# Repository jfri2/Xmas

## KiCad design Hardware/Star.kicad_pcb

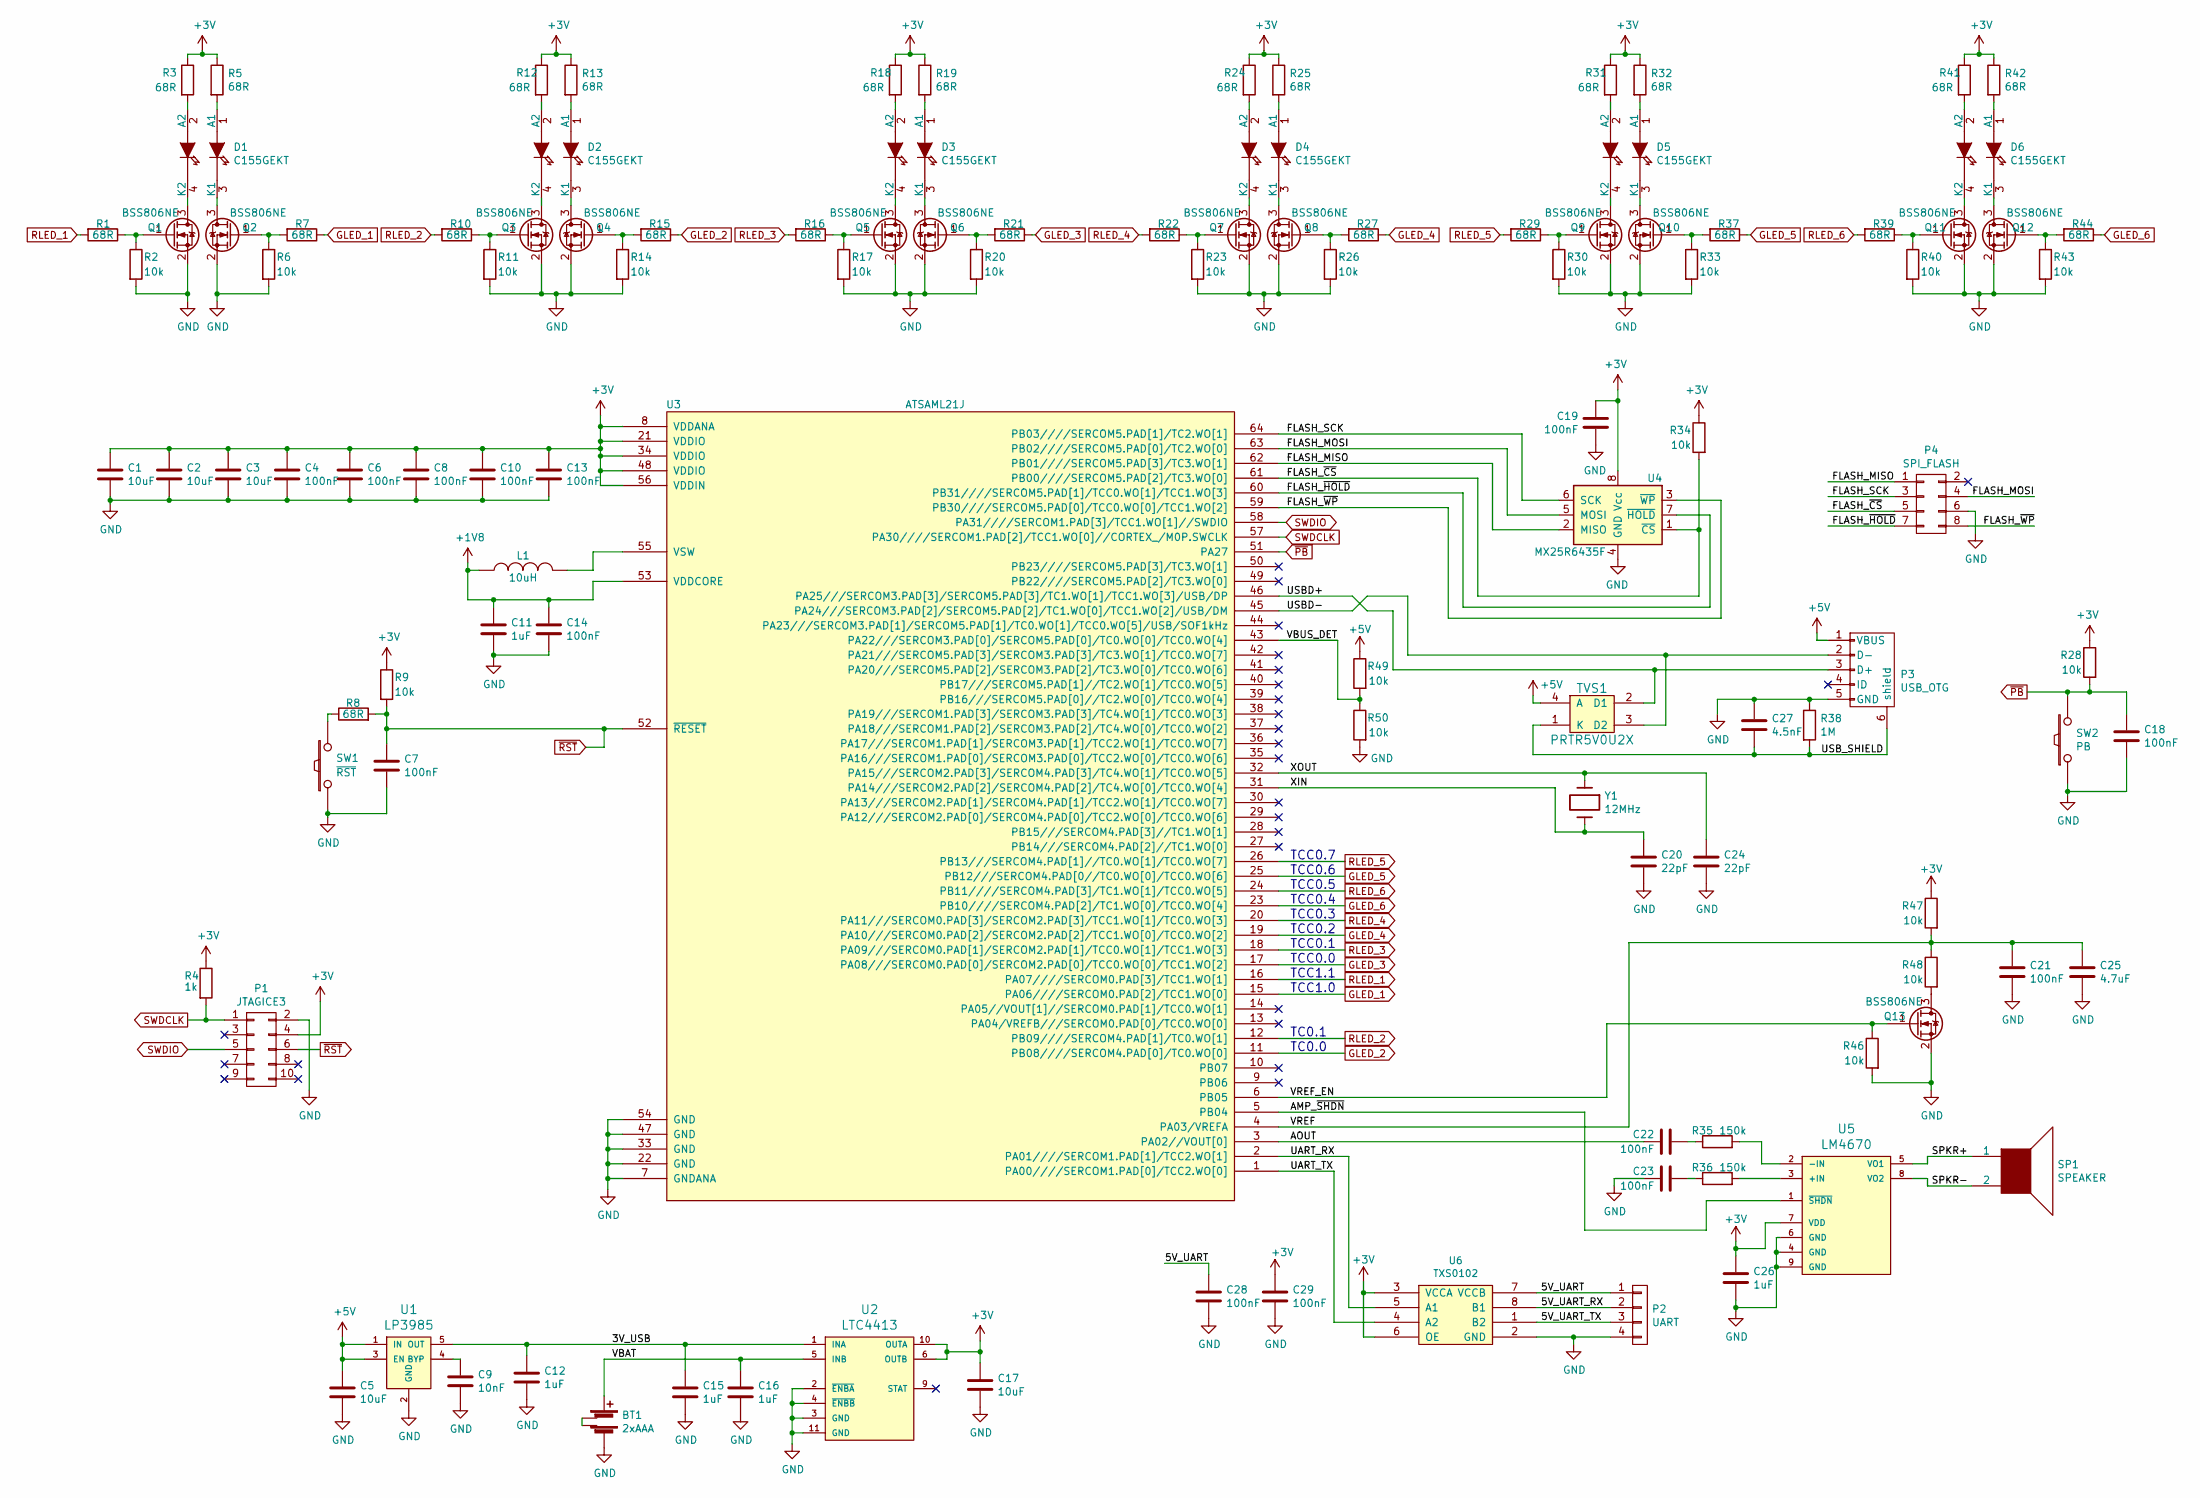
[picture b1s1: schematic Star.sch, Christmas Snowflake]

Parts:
BT1: 2xAAA; DUAL_AAA_HOLDER
C1, C2, C3, C5, C17: 10uF; C_1206
C4, C6, C7, C8, C10, C13, C14, C18, C19, C21, C22, C23, C28, C29: 100nF; C_0603
C9: 10nF; C_1206
C11, C12, C15, C16, C26: 1uF; C_0805
C20, C24: 22pF; C_0603
C25: 4.7uF; C_0805
C27: 4.5nF; C_0603
D1, D2, D3, D4, D5, D6: C155GEKT; LED2
L1: 10uH; Inductor_3mmx3mm
P1: JTAGICE3; Pin_Header_Straight_2x05_Pitch1.27mm
P2: UART; Pin_Header_Straight_1x04
P3: USB_OTG; conn_usb_B_micro_smd
P4: SPI_FLASH; Pin_Header_Straight_2x04
Q1, Q2, Q3, Q4, Q5, Q6, Q7, Q8, Q9, Q10, Q11, Q12, Q13: BSS806NE; SOT-23
R1, R3, R5, R7, R8, R10, R12, R13, R15, R16, R18, R19, R21, R22, R24, R25, R27, R29, R31, R32, R37, R39, R41, R42, R44: 68R; C_0603
R2, R6, R9, R11, R14, R17, R20, R23, R26, R28, R30, R33, R34, R40, R43, R46, R47, R48, R49, R50: 10k; C_0603
R4: 1k; C_0603
R35, R36: 150k; C_0603
R38: 1M; C_0603
SP1: SPEAKER; AS01808MR-R
SW1: ~RST; SW_SPST_TL3342
SW2: PB; SW_SPST_TL3342
TVS1: PRTR5V0U2X; SOT143B
U1: LP3985; SOT-23-5
U2: LTC4413; DFN-10-1EP_3x3mm_Pitch0.5mm
U3: ATSAML21J; QFN-64-1EP_9x9mm_Pitch0.5mm
U4: MX25R6435F; SOIJ-8_5.3x5.3mm_Pitch1.27mm
U5: LM4670; DFN-8-1EP_3x3mm_Pitch0.5mm
U6: TXS0102; MSOP-8_3x3mm_Pitch0.65mm
Y1: 12MHz; Crystal_SMD_5032_4Pads

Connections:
+1V8: C11.1, C14.1, L1.1, U3.53 (VDDCORE)
+3V: C1.1, C2.1, C3.1, C4.1, C6.1, C8.1, C10.1, C13.1, C17.1, C19.1, C26.1, C29.1, P1.4, R3.1, R4.1, R5.1, R9.1, R12.1, R13.1, R18.1, R19.1, R24.1, R25.1, R28.1, R31.1, R32.1, R34.1, R41.1, R42.1, R47.1, U2.6 (OUTB), U2.10 (OUTA), U3.8 (VDDANA), U3.21 (VDDIO), U3.34 (VDDIO), U3.48 (VDDIO), U3.56 (VDDIN), U4.8 (Vcc), U5.7 (VDD), U6.3 (VCCA), U6.6 (OE)
+5V: C5.1, P3.1 (VBUS), R49.1, TVS1.4 (A), U1.1 (IN), U1.3 (EN)
/3V_USB: C12.1, C15.1, U1.5 (OUT), U2.1 (INA)
/5V_UART: C28.1, P2.1, U6.7 (VCCB)
/5V_UART_RX: P2.2, U6.8 (B1)
/5V_UART_TX: P2.3, U6.1 (B2)
/AMP_~SHDN: U3.5 (PB04), U5.1 (~SHDN)
/AOUT: C22.1, U3.3 (PA02//VOUT[0])
/FLASH_MISO: P4.1, U3.62 (PB01////SERCOM5.PAD[3]/TC3.WO[1]), U4.2 (MISO)
/FLASH_MOSI: P4.4, U3.63 (PB02////SERCOM5.PAD[0]/TC2.WO[0]), U4.5 (MOSI)
/FLASH_SCK: P4.3, U3.64 (PB03////SERCOM5.PAD[1]/TC2.WO[1]), U4.6 (SCK)
/FLASH_~CS: P4.5, R34.2, U3.61 (PB00////SERCOM5.PAD[2]/TC3.WO[0]), U4.1 (~CS)
/FLASH_~HOLD: P4.7, U3.60 (PB31////SERCOM5.PAD[1]/TCC0.WO[1]/TCC1.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), U4.7 (~HOLD)
/FLASH_~WP: P4.8, U3.59 (PB30////SERCOM5.PAD[0]/TCC0.WO[0]/TCC1.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), U4.3 (~WP)
/SPKR+: SP1.1, U5.5 (VO1)
/SPKR-: SP1.2, U5.8 (VO2)
/UART_RX: U3.2 (PA01////SERCOM1.PAD[1]/TCC2.WO[1]), U6.5 (A1)
/UART_TX: U3.1 (PA00////SERCOM1.PAD[0]/TCC2.WO[0]), U6.4 (A2)
/USBD+: P3.3 (D+), TVS1.2 (D1), U3.46 (PA25///SERCOM3.PAD[3]/SERCOM5.PAD[3]/TC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)
/USBD-: P3.2 (D-), TVS1.3 (D2), U3.45 (PA24///SERCOM3.PAD[2]/SERCOM5.PAD[2]/TC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)
/USB_SHIELD: C27.2, P3.6 (shield), R38.2, TVS1.1 (K)
/VBAT: BT1.4, C16.1, U2.5 (INB)
/VBUS_DET: R49.2, R50.1, U3.43 (PA22///SERCOM3.PAD[0]/SERCOM5.PAD[0]/TC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)
/VREF: C21.1, C25.1, R47.2, R48.1, U3.4 (PA03/VREFA)
/VREF_EN: Q13.1 (G), R46.1, U3.6 (PB05)
/XIN: C20.1, U3.31 (PA14///SERCOM2.PAD[2]/SERCOM4.PAD[2]/TC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), Y1.2
/XOUT: C24.1, U3.32 (PA15///SERCOM2.PAD[3]/SERCOM4.PAD[3]/TC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), Y1.1
GLED_1: R7.1, U3.15 (PA06////SERCOM0.PAD[2]/TCC1.WO[0])
GLED_2: R15.1, U3.11 (PB08////SERCOM4.PAD[0]/TC0.WO[0])
GLED_3: R21.1, U3.17 (PA08///SERCOM0.PAD[0]/SERCOM2.PAD[0]/TC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)
GLED_4: R27.1, U3.19 (PA10///SERCOM0.PAD[2]/SERCOM2.PAD[2]/TC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)
GLED_5: R37.1, U3.25 (PB12///SERCOM4.PAD[0//TC0.WO[0]/TCC0.WO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)
GLED_6: R44.1, U3.23 (PB10////SERCOM4.PAD[2]/TC1.WO[0]/TCC0.W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)
GND: BT1.1, C1.2, C2.2, C3.2, C4.2, C5.2, C6.2, C7.2, C8.2, C9.2, C10.2, C11.2, C12.2, C13.2, C14.2, C15.2, C16.2, C17.2, C18.2, C19.2, C20.2, C21.2, C23.1, C24.2, C25.2, C26.2, C27.1, C28.2, C29.2, P1.2, P2.4, P3.5 (GND), P4.6, Q1.2 (S), Q2.2 (S), Q3.2 (S), Q4.2 (S), Q5.2 (S), Q6.2 (S), Q7.2 (S), Q8.2 (S), Q9.2 (S), Q10.2 (S), Q11.2 (S), Q12.2 (S), Q13.2 (S), R2.2, R6.2, R11.2, R14.2, R17.2, R20.2, R23.2, R26.2, R30.2, R33.2, R38.1, R40.2, R43.2, R46.2, R50.2, SW1.1, SW2.1, U1.2 (GND), U2.2 (~ENBA), U2.3 (GND), U2.4 (~ENBB), U2.11 (GND), U3.7 (GNDANA), U3.22 (GND), U3.33 (GND), U3.47 (GND), U3.54 (GND), U4.4 (GND), U5.4 (GND), U5.6 (GND), U5.9 (GND), U6.2 (GND)
unnamed: BT1.2, BT1.3
unnamed: C9.1, U1.4 (BYP)
unnamed: C22.2, R35.1
unnamed: C23.2, R36.1
unnamed: D1.1 (A1), R5.2
unnamed: D1.2 (A2), R3.2
unnamed: D1.3 (K1), Q2.3 (D)
unnamed: D1.4 (K2), Q1.3 (D)
unnamed: D2.1 (A1), R13.2
unnamed: D2.2 (A2), R12.2
unnamed: D2.3 (K1), Q4.3 (D)
unnamed: D2.4 (K2), Q3.3 (D)
unnamed: D3.1 (A1), R19.2
unnamed: D3.2 (A2), R18.2
unnamed: D3.3 (K1), Q6.3 (D)
unnamed: D3.4 (K2), Q5.3 (D)
unnamed: D4.1 (A1), R25.2
unnamed: D4.2 (A2), R24.2
unnamed: D4.3 (K1), Q8.3 (D)
unnamed: D4.4 (K2), Q7.3 (D)
unnamed: D5.1 (A1), R32.2
unnamed: D5.2 (A2), R31.2
unnamed: D5.3 (K1), Q10.3 (D)
unnamed: D5.4 (K2), Q9.3 (D)
unnamed: D6.1 (A1), R42.2
unnamed: D6.2 (A2), R41.2
unnamed: D6.3 (K1), Q12.3 (D)
unnamed: D6.4 (K2), Q11.3 (D)
unnamed: L1.2, U3.55 (VSW)
unnamed: Q1.1 (G), R1.1, R2.1
unnamed: Q2.1 (G), R6.1, R7.2
unnamed: Q3.1 (G), R10.1, R11.1
unnamed: Q4.1 (G), R14.1, R15.2
unnamed: Q5.1 (G), R16.1, R17.1
unnamed: Q6.1 (G), R20.1, R21.2
unnamed: Q7.1 (G), R22.1, R23.1
unnamed: Q8.1 (G), R26.1, R27.2
unnamed: Q9.1 (G), R29.1, R30.1
unnamed: Q10.1 (G), R33.1, R37.2
unnamed: Q11.1 (G), R39.1, R40.1
unnamed: Q12.1 (G), R43.1, R44.2
unnamed: Q13.3 (D), R48.2
unnamed: R8.1, SW1.2
unnamed: R35.2, U5.2 (-IN)
unnamed: R36.2, U5.3 (+IN)
RLED_1: R1.2, U3.16 (PA07////SERCOM0.PAD[3]/TCC1.WO[1])
RLED_2: R10.2, U3.12 (PB09////SERCOM4.PAD[1]/TC0.WO[1])
RLED_3: R16.2, U3.18 (PA09///SERCOM0.PAD[1]/SERCOM2.PAD[1]/TC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)
RLED_4: R22.2, U3.20 (PA11///SERCOM0.PAD[3]/SERCOM2.PAD[3]/TC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)
RLED_5: R29.2, U3.26 (PB13///SERCOM4.PAD[1]//TC0.WO[1]/TCC0.W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)
RLED_6: R39.2, U3.24 (PB11////SERCOM4.PAD[3]/TC1.WO[1]/TCC0.W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)
SWDCLK: P1.1, R4.2, U3.57 (PA30////SERCOM1.PAD[2]/TCC1.WO[0]//CORT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)
SWDIO: P1.5, U3.58 (PA31////SERCOM1.PAD[3]/TCC1.WO[1]//SWDIO)
~PB: C18.1, R28.2, SW2.2, U3.51 (PA27)
~RST: C7.1, P1.6, R8.2, R9.2, U3.52 (~RESET)

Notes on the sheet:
TCC0.7
TCC0.6
TCC0.5
TCC0.4
TCC0.3
TCC0.2
TCC0.1
TCC0.0
TC0.1
TC0.0
TCC1.0
TCC1.1

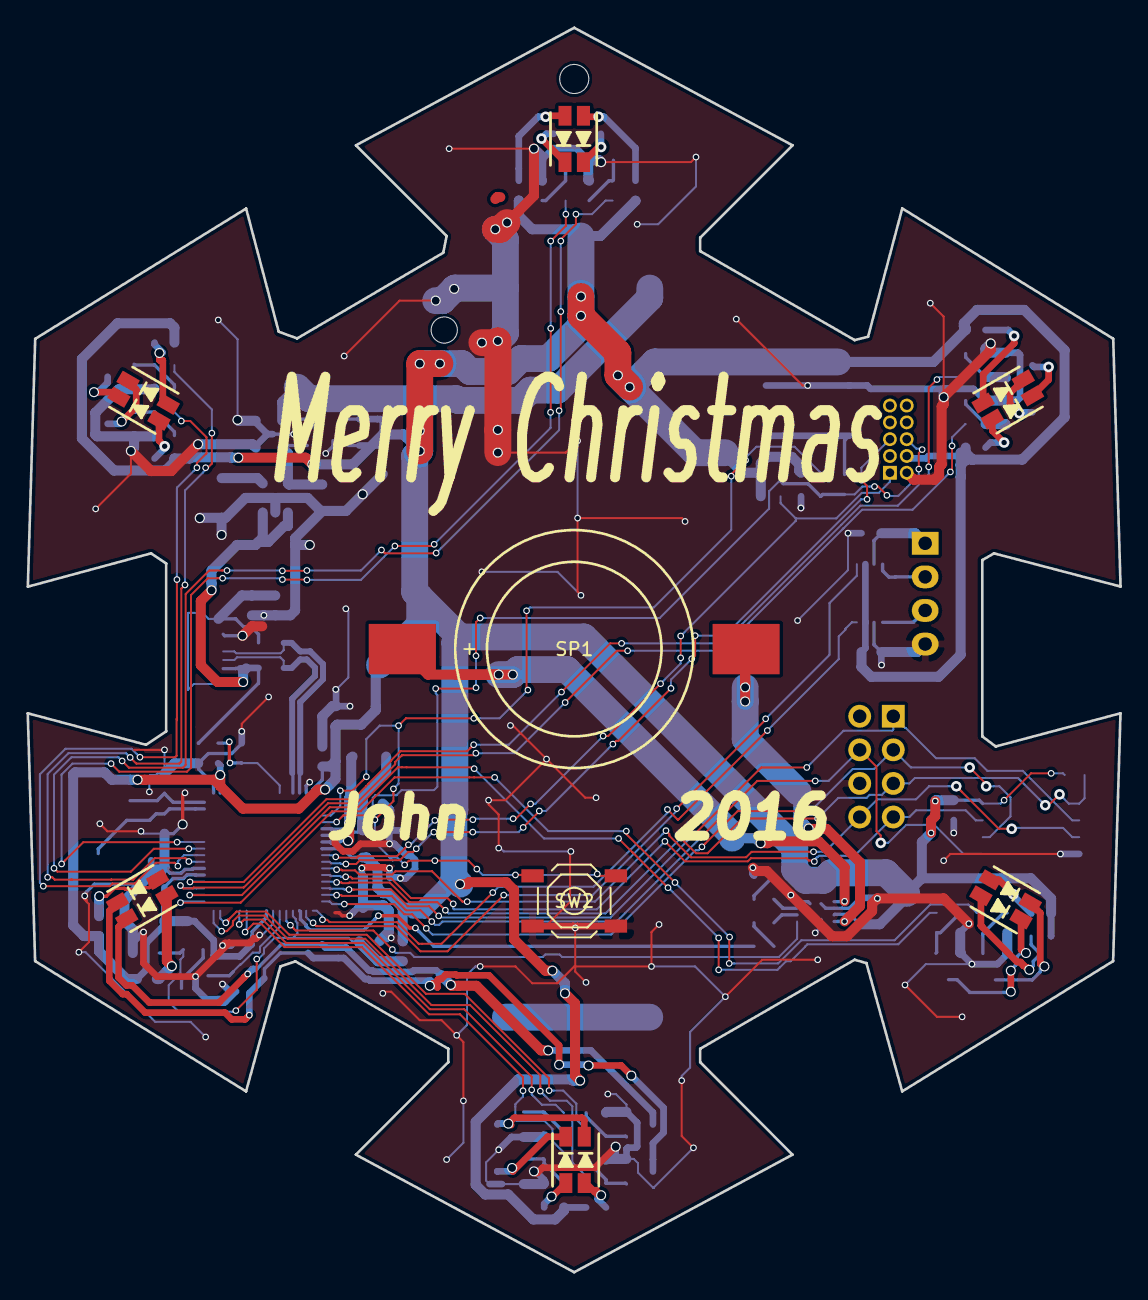
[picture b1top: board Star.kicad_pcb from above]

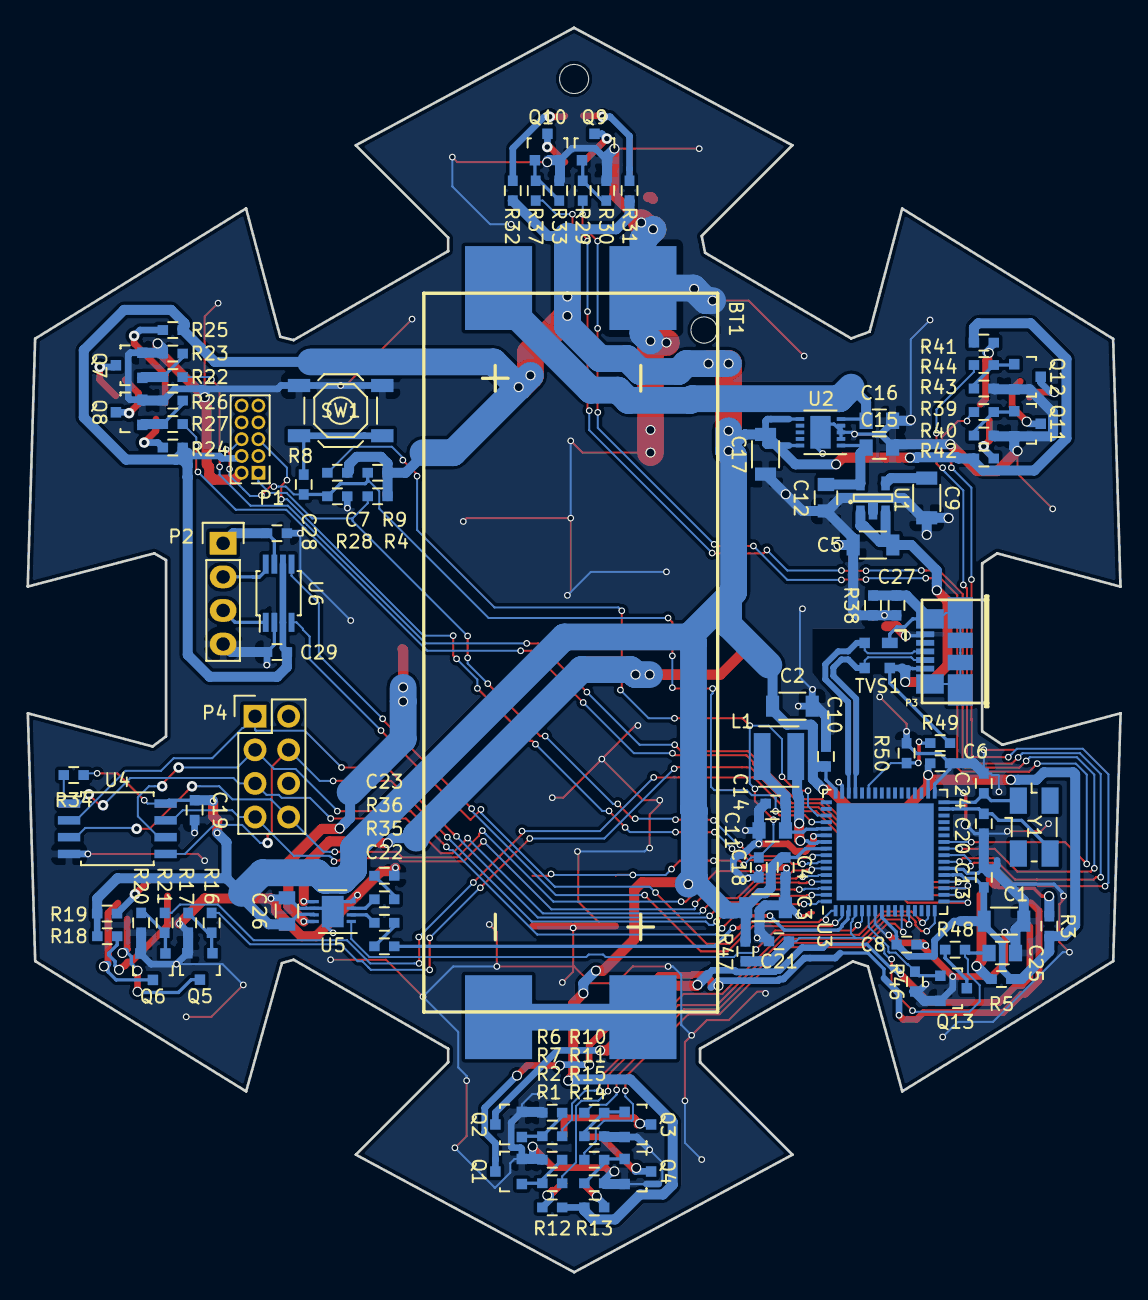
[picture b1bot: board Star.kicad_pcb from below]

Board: 2 copper layers, 82.6 x 94.1 mm, 114 parts (106 on the bottom side), 90 nets.

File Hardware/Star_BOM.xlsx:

| Reference | Quantity | 2x Qty | Value | Footprint | MFG# | DigiKey#
 | BT1 | 1 | 2 | 2xAAA | Custom | 1022 | 36-1022-ND
 | BT2 | 1 | 2 | CLIP | Custom | 1022C | 36-1022C-ND
 | C11 C12 C15 C16 C26 | 5 | 10 | 1uF | 0805 | CC0805KKX7R7BB105 | 311-1365-1-ND
 | C10 C13 C14 C18 C19 C21 C22 C23 C4 C6 C7 C8 C28 C29 | 14 | 28 | 100nF | 0603 | C0603C104M5RACTU | 399-7845-1-ND
 | C20 C24 | 2 | 4 | 22pF | 0603 | C0603C220F1GACTU | 399-11145-1-ND
 | C25 | 1 | 2 | 4.7uF | 0805 | GRM21BR71A475KA73K | 490-6479-1-ND
 | C27 | 1 | 2 | 4.5nF | 0603 | CL10B472KB8NNNC | 1276-1098-1-ND
 | C1 C17 C2 C3 C5 | 5 | 10 | 10uF | 1206 | CL31B106KAHNNNE | 1276-1804-1-ND
 | C9 | 1 | 2 | 10nF | 0603 | CC0603KRX7R9BB103 | 311-1085-1-ND
 | D1 D2 D3 D4 D5 D6 | 6 | 12 | C155GEKT | 1210 2xLED | LTST-C155KGJRKT | 160-1409-1-ND
 | L1 | 1 | 2 | 10uH | Custom | LQH3NPN100MJ0L | 490-11681-1-ND
 | P1 | 1 | 2 | JTAGICE3 | 0.05" | 62201021121 | 732-5374-ND
 | P2 | 1 | 2 | UART | 0.1"
 | P3 | 1 | 2 | USB_OTG | Custom | 10118192-0001LF | 609-4613-1-ND
 | P4 | 1 | 2 | SPI_FLASH | 0.1"
 | Q1 Q10 Q11 Q12 Q2 Q3 Q4 Q5 Q6 Q7 Q8 Q9 Q13 | 13 | 26 | BSS806NE | SOT-23 | BSS806NEH6327XTSA1 | BSS806NEH6327XTSA1CT-ND
 | R1 R10 R12 R13 R15 R16 R18 R19 R21 R22 R24 R25 R27 R29 R3 R31 R32 R37 R39 R41 R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 | 25 | 50 | 68R | 0603 | ESR03EZPJ680 | RHM68DCT-ND
 | R11 R14 R17 R2 R20 R23 R26 R28 R30 R33 R34 R40 R43 R6 R9 R46 R47 R48 R49 R50 | 20 | 40 | 10k | 0603 | RC0603JR-0710KL | 311-10KGRCT-ND
 | R35 R36 | 2 | 4 | 150k | 0603 | RC0603JR-07150KL | 311-150KGRCT-ND
 | R38 | 1 | 2 | 1M | 0603 | RC0603JR-071ML | 311-1.0MGRCT-ND
 | R4 | 1 | 2 | 1k | 0603 | RC0603JR-071KL | 311-1.0KGRCT-ND
 | SP1 | 1 | 2 | SPEAKER | Custom | AS01808MR-R | 668-1228-ND
 | SW1 | 1 | 2 | ~RST | 3342 | TL3342F160QG/TR | EG2531CT-ND
 | SW2 | 1 | 2 | WKUP | 3342 | TL3342F160QG/TR | EG2531CT-ND
 | U1 | 1 | 2 | LP3985 | SOT-23-5 | LP3985IM5X-3.0/NOPB | LP3985IM5X-3.0/NOPBCT-ND
 | U2 | 1 | 2 | LTC4413 | 10-WFDFN Exposed Pad | LTC4413EDD#TRPBF | LTC4413EDD#TRPBFCT-ND
 | U3 | 1 | 2 | ATSAML21J | 64-QFN (9x9) | ATSAML21J18B-MUT | ATSAML21J18B-MUTCT-ND
 | U4 | 1 | 2 | MX25R6435F | SOIJ-8 | MX25R6435FM2IH0 | 1092-1171-ND
 | U5 | 1 | 2 | LM4670 | 8-WSON (3x3) | LM4670SD/NOPB | 296-35178-1-ND
 | U6 | 1 | 2 | TXS0102 | MSOP-8 | TXS0102DCTT | 296-32603-1-ND
 | Y1 | 1 | 2 | 12MHz | Custom | FQ5032B-12.000 | 631-1023-1-ND
 | TVS1 | 1 | 2 | PRTR5V0U2X | TO-253-4 | PRTR5V0U2X,215 | 568-4140-1-ND

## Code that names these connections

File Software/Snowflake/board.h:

/** @file board.h
* @brief Board specific definitions for snowflake project
*
* @par
* COPYRIGHT NOTICE: (c) 2017 John Fritz
* All rights reserved
*/

#ifndef _BOARD_H
#define _BOARD_H

#include <stdbool.h>
#include <sam.h>

///////////////////////////////////////////////////////////////////////////////
// CPU Frequency Definitions
///////////////////////////////////////////////////////////////////////////////
#ifndef F_CPU
#define F_CPU    // @todo
#endif

///////////////////////////////////////////////////////////////////////////////
// GPIO Definitions
///////////////////////////////////////////////////////////////////////////////

// LED Definitions
#define LED_R1_PIN      PIN_PA07
#define LED_G1_PIN      PIN_PA06
#define LED_R2_PIN      PIN_PB09
#define LED_G2_PIN      PIN_PB08
#define LED_R3_PIN      PIN_PA09
#define LED_G3_PIN      PIN_PA08
#define LED_R4_PIN      PIN_PA11
#define LED_G4_PIN      PIN_PA10
#define LED_R5_PIN      PIN_PB13
#define LED_G5_PIN      PIN_PB12
#define LED_R6_PIN      PIN_PB11
#define LED_G6_PIN      PIN_PB10

// Pushbutton Definitions
#define PB_PIN      PIN_PA27

// Analog Voltage Reference Definitions
#define VREF_PIN    PIN_PA03

// Audio Amplifier Shutdown Definitions
#define AMP_SHDN_PIN        PIN_PB04

// USB VBUS Detect Definitions
#define USB_VBUS_DET_PIN    PIN_PA22

// Flash Definitions
#define FLASH_CS_PIN        PIN_PB00
#define FLASH_HOLD_PIN      PIN_PB31
#define FLASH_WP_PIN        PIN_PB30

#endif /* _BOARD_H */

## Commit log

2016-12-07 :confetti_ball: Added .gitattributes & .gitignore files
2016-12-08 stuff
2016-12-08 Finished routing
2016-12-09 Cleaned up gnd pours
2016-12-09 Silkscreened board
2016-12-13 Finished hardware design
2017-01-01 Finished hardware, started software
2017-01-21 Started boilerplate software
2017-01-22 Started board bringup
2017-01-23 Application software start
2017-01-24 Changed module structure to better encapsulate everything
2017-01-27 Got some ugly GPIO init stuff working in modules
2017-01-30 Stopped dev using ASF, started own drivers etc., got a USB example working in START
2017-01-30 Added project file framework. Need to resolve linker issues.
2017-02-01 Fixed linker issues, added gpio example
2017-02-01 Removed extra copies of lib source files
2017-02-09 Refactored typedefs, started clock driver
2017-02-09 Updated clock and gpio stuff
2017-02-11 Refactored driver stuff
